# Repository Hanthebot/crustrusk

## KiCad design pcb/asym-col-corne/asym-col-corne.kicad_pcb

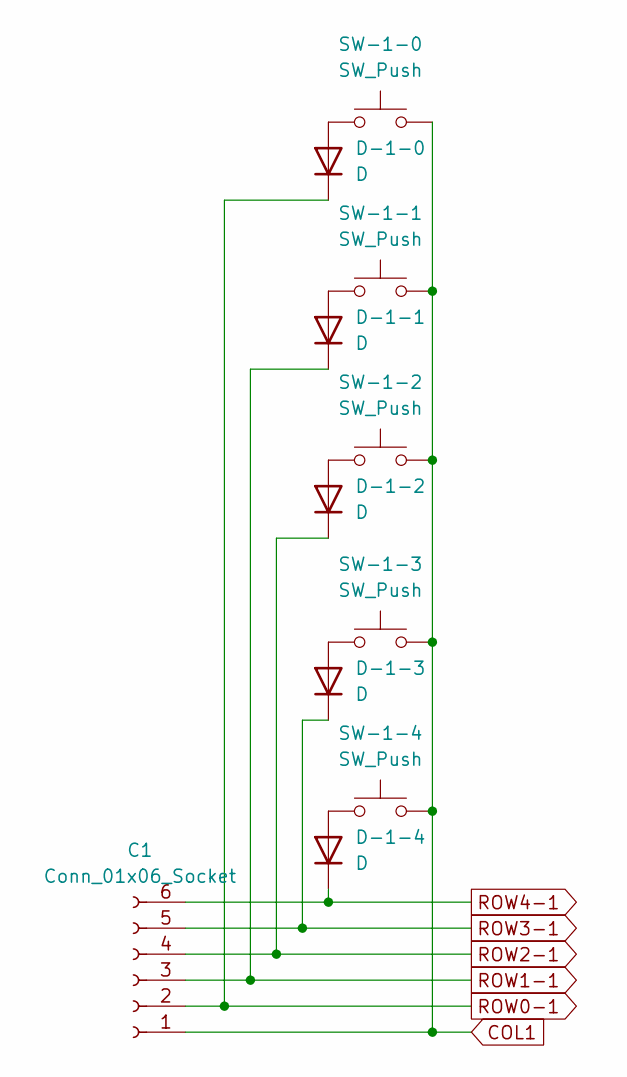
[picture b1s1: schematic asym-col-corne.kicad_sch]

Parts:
C1: Conn_01x06_Socket; reversible JST_PH_S6B-PH-K_1x06_P2.00mm_Horizontal
D-1-0, D-1-1, D-1-2, D-1-3, D-1-4: D; Diode_TH_SMD_REVERSIBLE
SW-1-0, SW-1-1, SW-1-2, SW-1-3, SW-1-4: SW_Push; Kailh_hotswap_only_socket_MX_optional_reversible-MIRROR

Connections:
COL1: C1.1, SW-1-0.2, SW-1-1.2, SW-1-2.2, SW-1-3.2, SW-1-4.2
unnamed: D-1-0.2 (A), SW-1-0.1
unnamed: D-1-1.2 (A), SW-1-1.1
unnamed: D-1-2.2 (A), SW-1-2.1
unnamed: D-1-3.2 (A), SW-1-3.1
unnamed: D-1-4.2 (A), SW-1-4.1
ROW0-1: C1.2, D-1-0.1 (K)
ROW1-1: C1.3, D-1-1.1 (K)
ROW2-1: C1.4, D-1-2.1 (K)
ROW3-1: C1.5, D-1-3.1 (K)
ROW4-1: C1.6, D-1-4.1 (K)

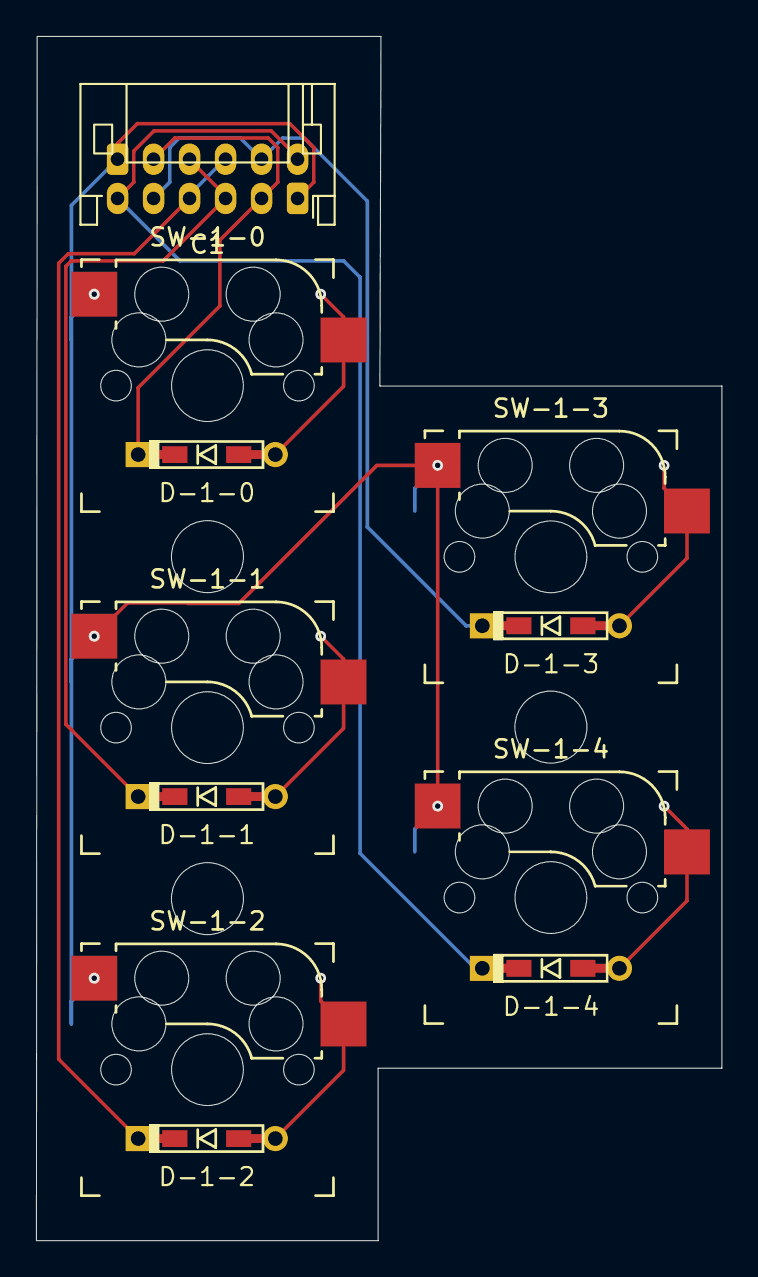
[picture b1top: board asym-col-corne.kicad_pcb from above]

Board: 2 copper layers, 38.1 x 66.9 mm, 11 parts (0 on the bottom side), 11 nets.
